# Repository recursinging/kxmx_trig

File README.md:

# kxmx_trig

A piezo drum trigger module, intended to collect and send a few drum events to kxmx_hirn where they can be abused.

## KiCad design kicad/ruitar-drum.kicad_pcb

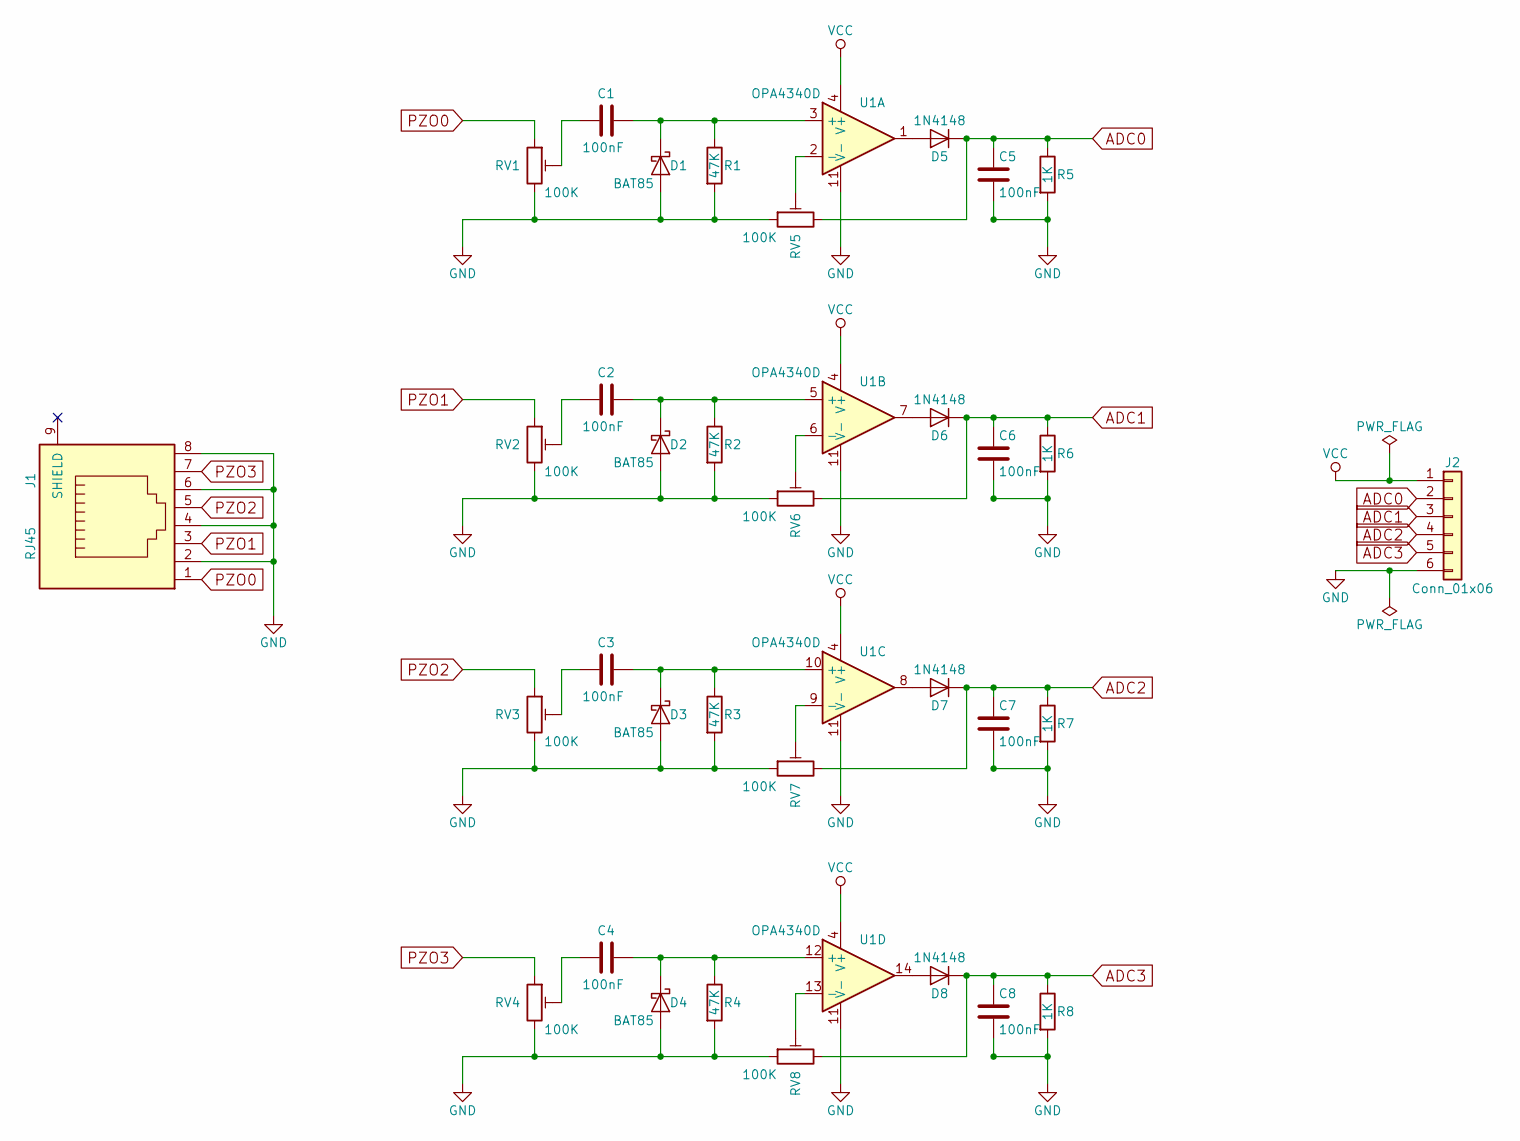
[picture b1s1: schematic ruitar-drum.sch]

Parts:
C1, C2, C3, C4, C5, C6, C7, C8: 100nF; C_0805
D1, D2, D3, D4: BAT85; D_DO-35_SOD27_P7.62mm_Horizontal
D5, D6, D7, D8: 1N4148; D_0805
J1: RJ45; RJ45_8
J2: Conn_01x06; Pin_Header_Straight_1x06_Pitch2.54mm
R1, R2, R3, R4: 47K; R_0805
R5, R6, R7, R8: 1K; R_0805
RV1, RV2, RV3, RV4, RV5, RV6, RV7, RV8: 100K; Potentiometer_Triwood_RM-065
U1: OPA4340D; SOIC-14_3.9x8.7mm_Pitch1.27mm

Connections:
ADC0: C5.1, D5.1 (K), J2.2, R5.1, RV5.3
ADC1: C6.1, D6.1 (K), J2.3, R6.1, RV6.3
ADC2: C7.1, D7.1 (K), J2.4, R7.1, RV7.3
ADC3: C8.1, D8.1 (K), J2.5, R8.1, RV8.3
GND: C5.2, C6.2, C7.2, C8.2, D1.2 (A), D2.2 (A), D3.2 (A), D4.2 (A), J1.2, J1.4, J1.6, J1.8, J2.6, R1.2, R2.2, R3.2, R4.2, R5.2, R6.2, R7.2, R8.2, RV1.3, RV2.3, RV3.3, RV4.3, RV5.1, RV6.1, RV7.1, RV8.1, U1.11 (V-)
unnamed: C1.1, RV1.2
unnamed: C1.2, D1.1 (K), R1.1, U1.3 (+)
unnamed: C2.1, RV2.2
unnamed: C2.2, D2.1 (K), R2.1, U1.5 (+)
unnamed: C3.1, RV3.2
unnamed: C3.2, D3.1 (K), R3.1, U1.10 (+)
unnamed: C4.1, RV4.2
unnamed: C4.2, D4.1 (K), R4.1, U1.12 (+)
unnamed: D5.2 (A), U1.1
unnamed: D6.2 (A), U1.7
unnamed: D7.2 (A), U1.8
unnamed: D8.2 (A), U1.14
unnamed: RV5.2, U1.2 (-)
unnamed: RV6.2, U1.6 (-)
unnamed: RV7.2, U1.9 (-)
unnamed: RV8.2, U1.13 (-)
PZO0: J1.1, RV1.1
PZO1: J1.3, RV2.1
PZO2: J1.5, RV3.1
PZO3: J1.7, RV4.1
VCC: J2.1, U1.4 (V+)

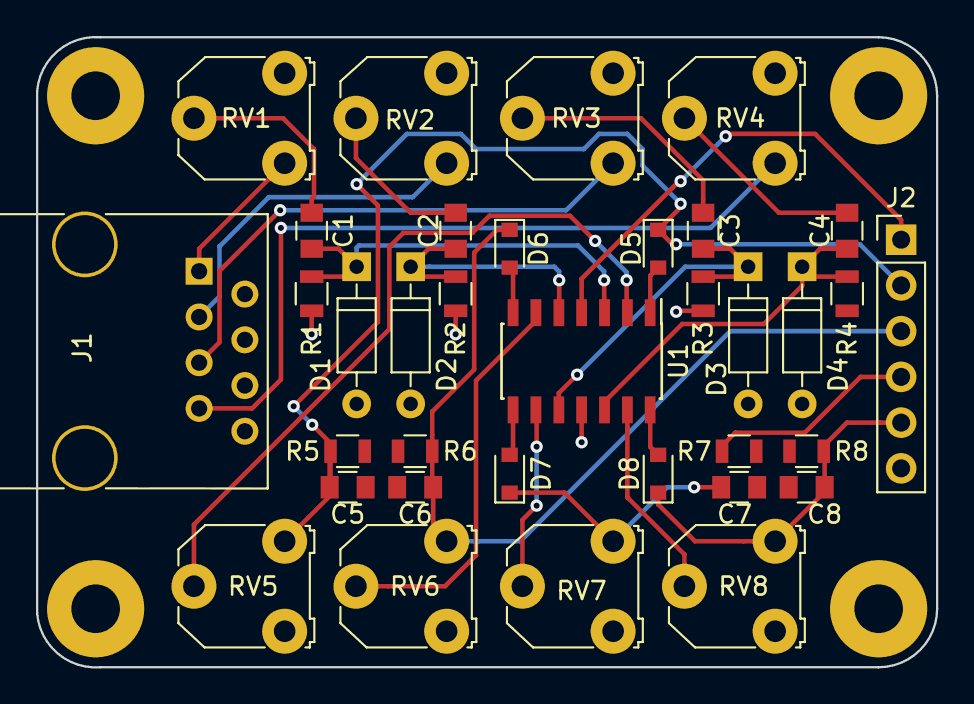
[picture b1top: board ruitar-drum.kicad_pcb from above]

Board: 2 copper layers, 50.0 x 35.0 mm, 35 parts (0 on the bottom side), 26 nets.

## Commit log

2018-08-31 Restructure. Rename. Document.
